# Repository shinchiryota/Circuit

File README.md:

# Circuit
2022以降の回路をまとめる

## [諸注意](諸注意)
+ [使用するソフトウェア](諸注意/使用するソフトウェア/readme.md)
+ [ファイル構成](諸注意/ファイル構成/readme.md)
+ [命名規則](諸注意/命名規則/readme.md)

## [2022](https://github.com/shinchiryota/Circuit/blob/main/2022/README.md)
+ servo_solenoidvalve_of_Tatebayashi

+ unitbase_keinz_2022

+ controller_keinz_2022
## [2023](https://github.com/shinchiryota/Circuit/blob/main/2023/README.md)
+ controller_keinz_2023

+ sensormain_of_sawada

+ servosolenoidvalve_of_tanbo

+ unitbase_anayuki
## [2024](https://github.com/shinchiryota/Circuit/blob/main/2024/README.md)
+ Power_of_Exodia

+ Unitbase_of_exoia
+ ### [nhk2024](https://github.com/shinchiryota/Circuit/blob/main/2024/nhk2024/README.md)

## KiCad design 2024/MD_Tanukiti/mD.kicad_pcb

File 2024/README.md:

# 2024年度の回路
+ Power_of_Exodia
 
+ Unitbase_of_exodia
## [nhk2024](https://github.com/shinchiryota/Circuit/tree/main/2024/nhk2024)

# [始めに戻る](https://github.com/shinchiryota/Circuit/blob/main/README.md)

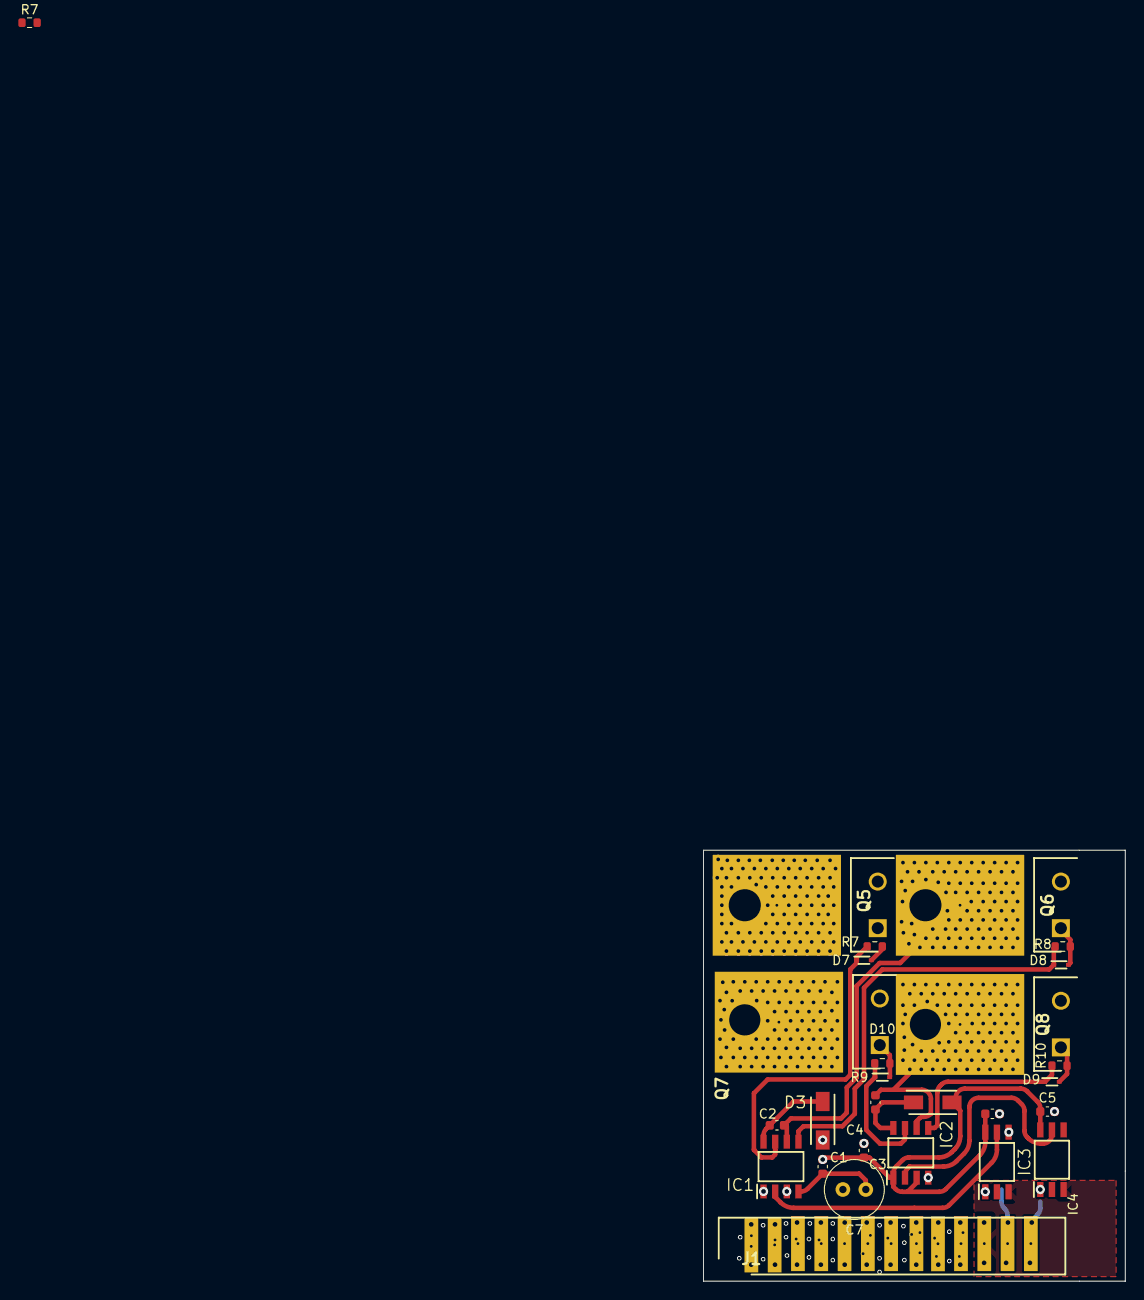
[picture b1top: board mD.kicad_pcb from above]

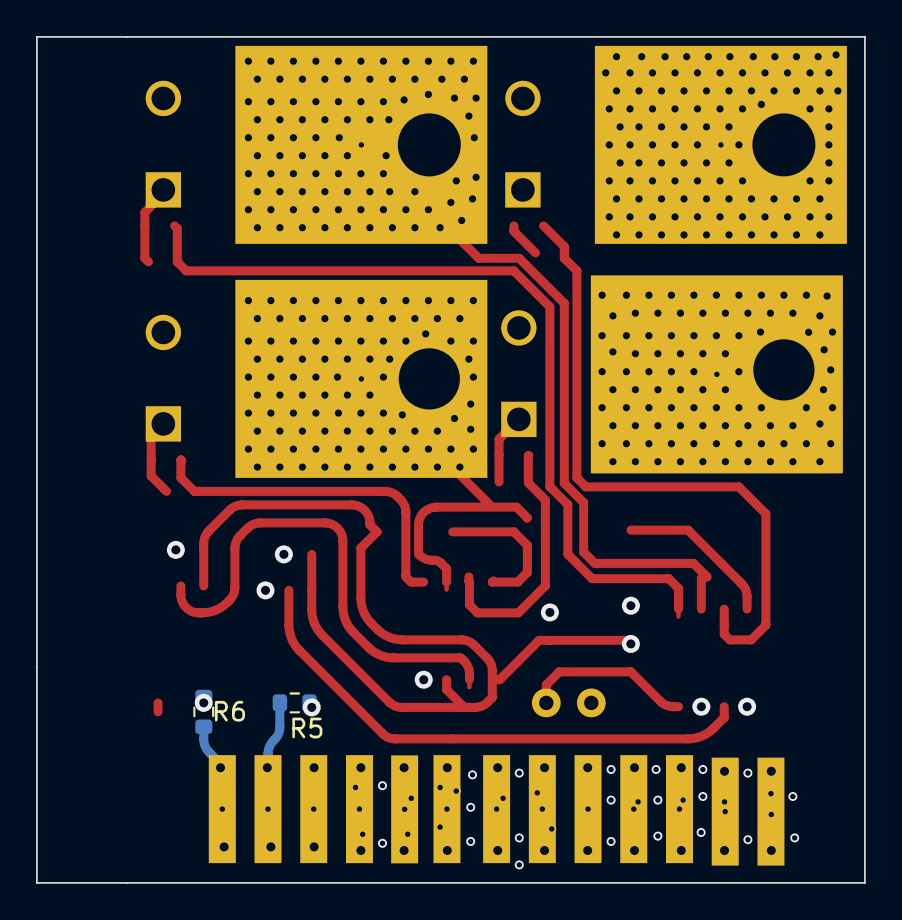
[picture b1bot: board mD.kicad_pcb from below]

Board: 2 copper layers, 46.0 x 47.0 mm, 29 parts (2 on the bottom side), 22 nets.

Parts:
C1: C_1u; C_0603_1608Metric
C2, C4: C0.1u; C_0603_1608Metric
C3: C1u; C_0603_1608Metric
C5, C6: 0.1u; C_0603_1608Metric
C7: 100uF; C_Radial_D6.3mm_H11.0mm_P2.50mm
D3, D6: SS14; DIOM5126X250N
D7, D8, D9, D10: BAT43; SODFL1608X70N
IC1, IC2: IRS2008SPBF; SOIC127P600X175-8N
IC3, IC4: TLP152_E_T; SOIC127P700X220-6N
J1: HIF3FB-26DA-2.54DSA_71_; RHDR26W71P254_2X13_3759X600X980P
Q5, Q6, Q7, Q8: EKI04027; eki04027
R5, R6: R150; R_0603_1608Metric
R7, R7#2, R8, R9, R10: 1k; R_0603_1608Metric

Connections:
/12V: C1.1, C3.1, C5.1, C6.1, C7.2, D3.2 (A), D6.2 (A), IC1.1 (VCC), IC1.3 (~SD), IC2.1 (VCC), IC2.3 (~SD), IC3.6 (VCC), IC4.6 (VCC), J1.1, J1.4, J1.6, J1.8, J1.10, Q5.2, Q7.2
/12V_GND: J1.12, J1.14, J1.16, J1.18, J1.20, Q6.3, Q8.3
/GND: IC3.3 (CATHODE), IC4.3 (CATHODE), J1.22
/GND_12V: C1.2, C3.2, C5.2, C6.2, C7.1, IC1.4 (COM), IC2.4 (COM), IC3.4 (GND), IC4.4 (GND)
/LH: D7.1 (K), IC1.7 (HO), R7.2, R7#2.2
/LIN: IC1.2 (IN), IC3.5 (VO)
/LL: D8.1 (K), IC1.5 (LO), R8.1
/LS: C2.2, IC1.6 (VS), Q5.3, Q6.2
/PWML: J1.24, R5.2
/PWMR: J1.26, R6.2
/RH: D10.1 (K), IC2.7 (HO), R9.2
/RIN: IC2.2 (IN), IC4.5 (VO)
/RL: D9.1 (K), IC2.5 (LO), R10.2
/RS: C4.2, IC2.6 (VS), Q7.3, Q8.2
unnamed: C2.1, D3.1 (K), IC1.8 (VB)
unnamed: C4.1, D6.1 (K), IC2.8 (VB)
unnamed: D7.2 (A), Q5.1, R7.1, R7#2.1
unnamed: D8.2 (A), Q6.1, R8.2
unnamed: D9.2 (A), Q8.1, R10.1
unnamed: D10.2 (A), Q7.1, R9.1
unnamed: IC3.1 (ANODE), R5.1
unnamed: IC4.1 (ANODE), R6.1

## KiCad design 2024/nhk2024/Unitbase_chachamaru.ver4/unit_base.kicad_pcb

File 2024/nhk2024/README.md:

# 高専ロボコン2024で使った回路
+ Controller 

+ Sensormain

+ Unitbase

+ Servosolenoidvalve

+ FEP02 

# [始めに戻る](https://github.com/shinchiryota/Circuit/blob/main/README.md)

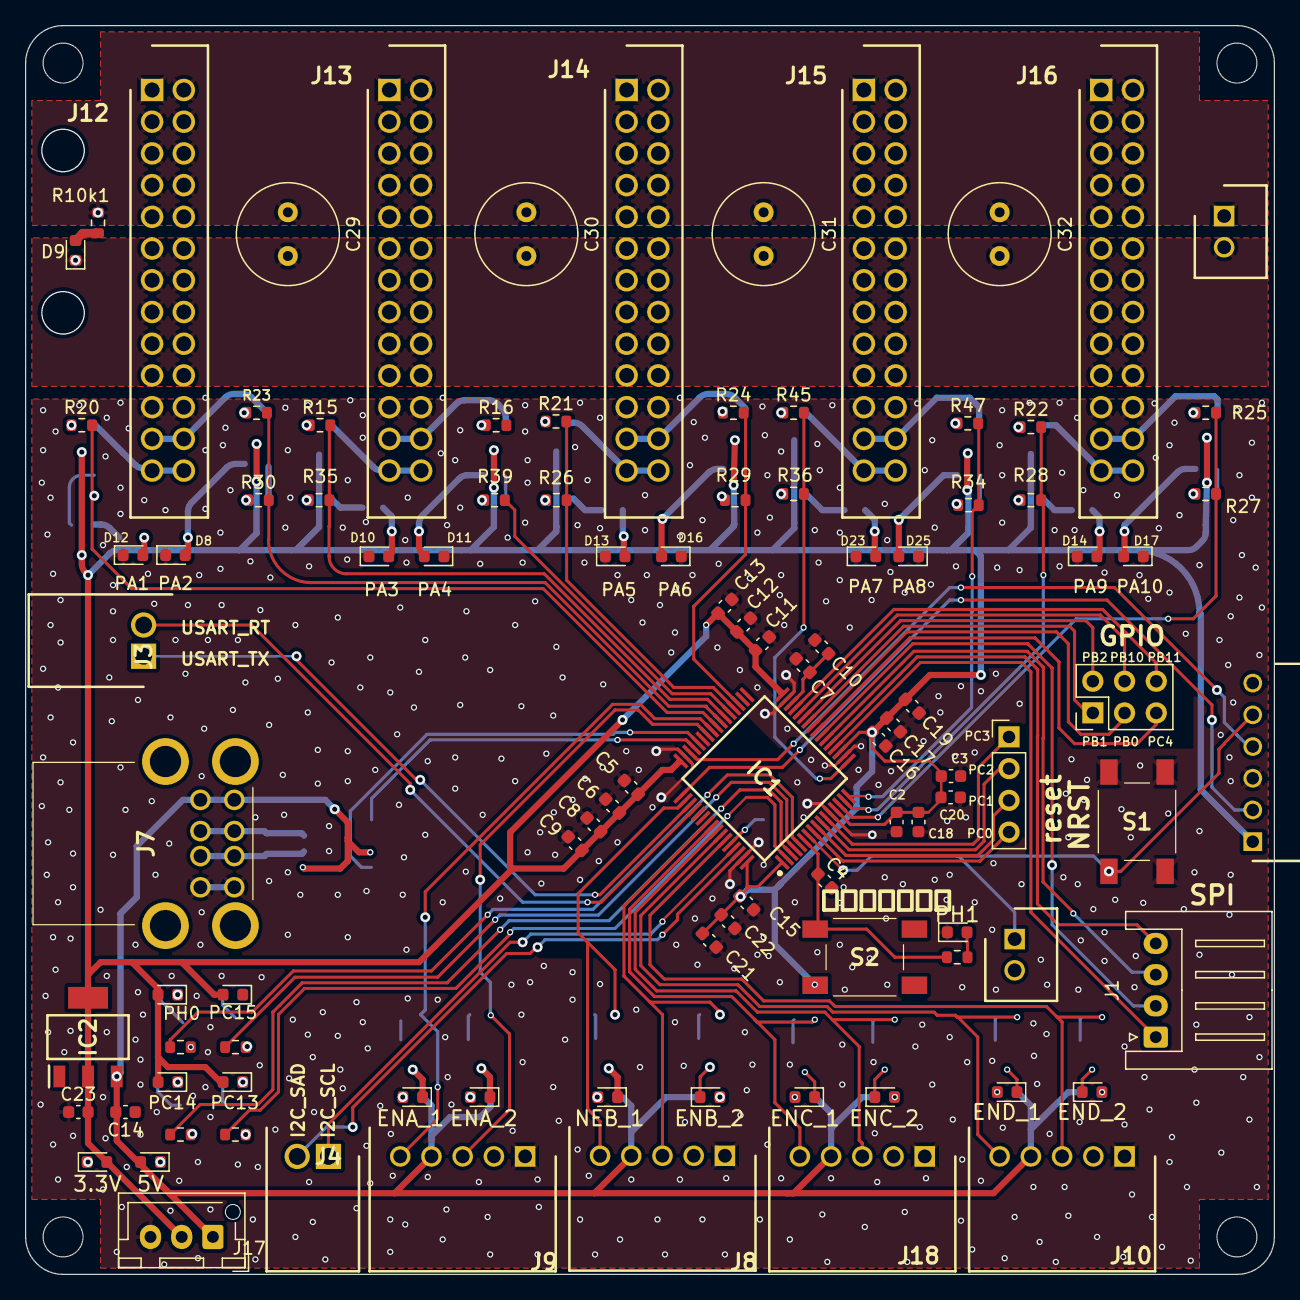
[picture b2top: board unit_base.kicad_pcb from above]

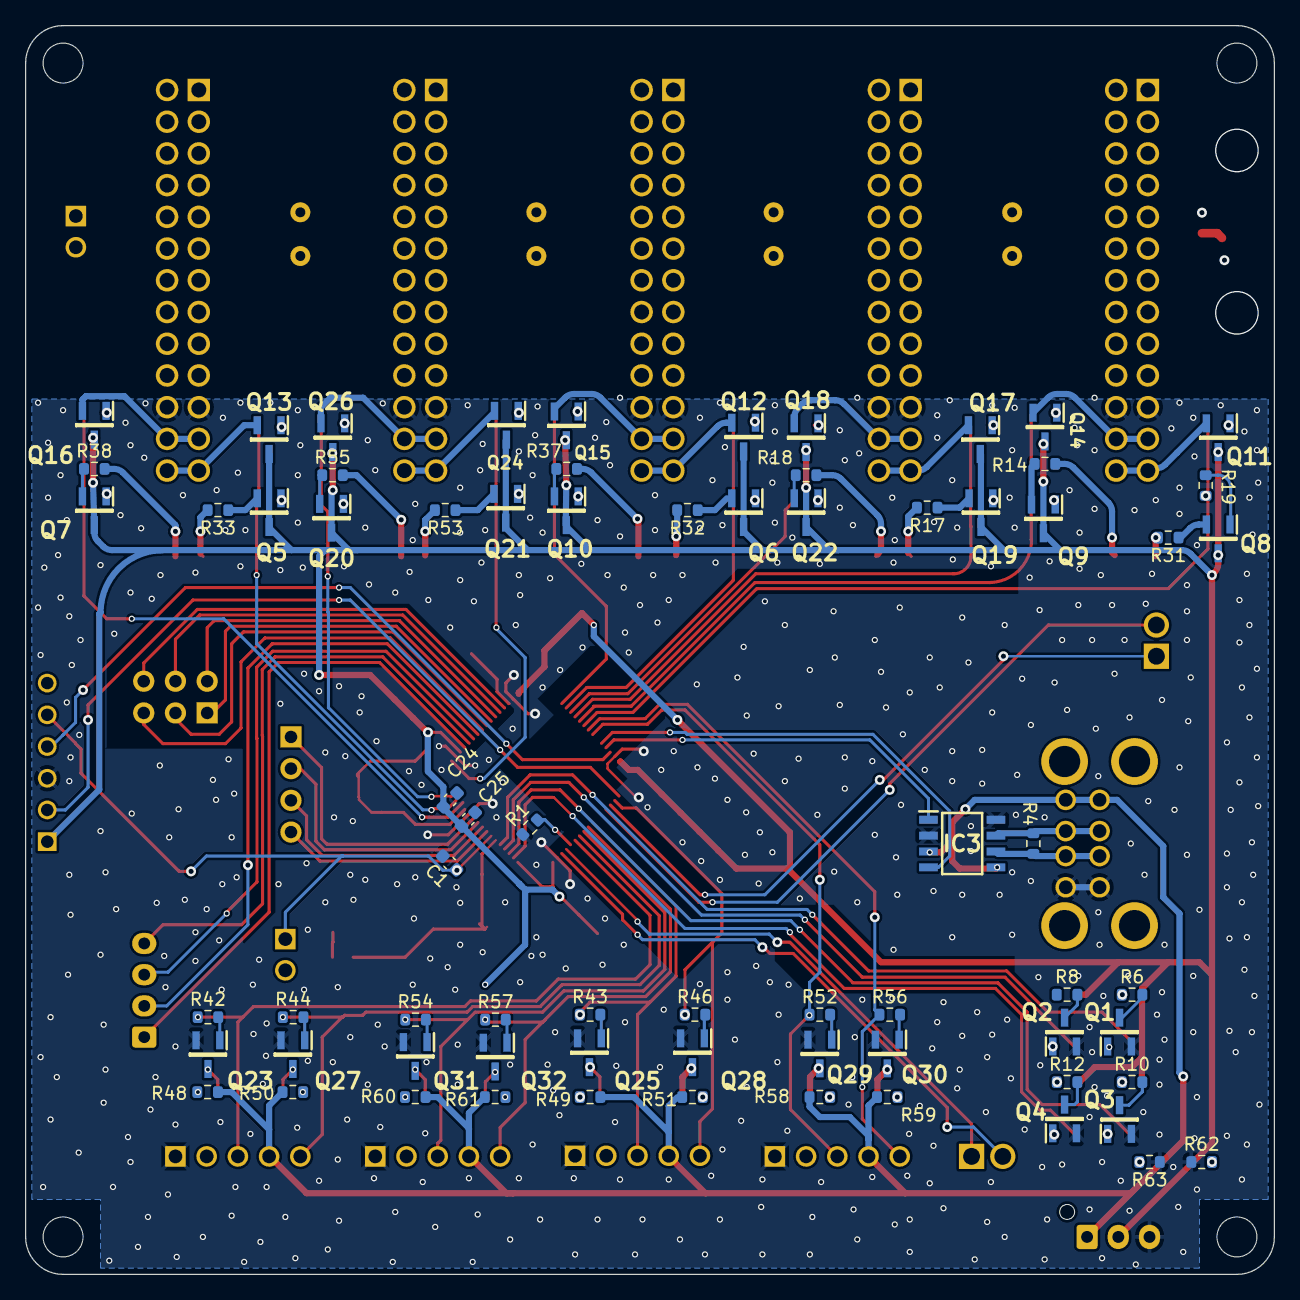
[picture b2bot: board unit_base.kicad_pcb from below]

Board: 2 copper layers, 100.0 x 100.0 mm, 169 parts (71 on the bottom side), 136 nets.

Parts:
3.3V, 5V: LED; LED_0603_1608Metric
C1, C4: C0.1u; C_0603_1608Metric
C2, C18, C24: 100n; C_0603_1608Metric
C3, C20, C25: 1u; C_0603_1608Metric
C5, C6, C8, C9, C11, C12, C13, C14, C15, C16, C17, C19: C100n; C_0603_1608Metric
C7, C10: C2.2u; C_0603_1608Metric
C21: C4.7u; C_0603_1608Metric
C22: 100u; C_0603_1608Metric
C23: C10u; C_0603_1608Metric
C29, C30, C31, C32: C; C_Radial_D8.0mm_H11.5mm_P3.50mm
D8, D9, D10, D11, D12, D13, D14, D16, D17, D23, D25: LED; LED_0603_1608Metric
ENA_1, ENA_2: LED; LED_0603_1608Metric
ENB_2: LED; LED_0603_1608Metric
ENC_1, ENC_2: LED; LED_0603_1608Metric
END_1, END_2: LED; LED_0603_1608Metric
IC1: STM32F732RET6; QFP50P1200X1200X160-64N
IC2: LM317_SOT-223_; SOT230P700X180-4N
IC3: NCV7351D1ER2G; SOIC127P600X175-8N
J1: S4B-XH-A_LF__SN_; JST_XH_S4B-XH-A_1x04_P2.50mm_Horizontal
J2, J11: B2B-XH-A; SHDR2W64P0X250_1X2_740X575X700P
J3, J4: S2B-XH-A_LF__SN_; SHDRRA2W80P0X250_1X2_740X1150X610P
J6: FH-1X06RG; RHDRRA6W58P0X254_1X6_1549X850X265P
J7: USB-4AF203AS; USB4AF203AS
J8, J9, J10, J18: S5B-XH-A_LF__SN_; SHDRRA5W64P0X250_1X5_1490X1150X610P
J12, J13, J14, J15, J16: HIF3FB-26DA-2.54DSA_71_; RHDR26W71P254_2X13_3759X600X980Pソケット
J17: B3B-XH-A; JST_XH_B3B-XH-AM_1x03_P2.50mm_Vertical
NEB_1: LED; LED_0603_1608Metric
PC13, PC14, PC15: LED; LED_0603_1608Metric
PH0, PH1: LED; LED_0603_1608Metric
Q1, Q2, Q3, Q4, Q5, Q6, Q7, Q8, Q9, Q10, Q11, Q12, Q13, Q14, Q15, Q16, Q17, Q18, Q19, Q20, Q21, Q22, Q23, Q24, Q25, Q26, Q27, Q28, Q29, Q30, Q31, Q32: 2SC2712-GR_TE85L,F; SOT95P260X156-3N
R1: R10k; R_0603_1608Metric
R2, R4, R6, R7, R8, R9, R10, R10k1, R11, R12, R13, R14, R15, R16, R17, R18, R19, R20, R21, R22, R23, R24, R25, R26, R27, R28, R29, R30, R31, R32, R33, R34, R35, R36, R37, R38, R39, R42, R43, R44, R45, R46, R47, R48, R49, R50, R51, R52, R53, R54, R55, R56, R57, R58, R59, R60, R61, R62, R63: R; R_0603_1608Metric
S1, S2: TSHA-T-2.5B2-19E; TSHAT25B219E

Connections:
3.3V: 3.3V.2 (A), C2.1, C3.1, C5.1, C6.1, C8.1, C9.1, C11.1, C12.1, C13.1, C15.1, C16.1, C17.1, C18.1, C19.1, C20.1, C21.1, C22.1, C23.2, C24.1, C25.1, IC1.1 (VBAT), IC1.13 (VREF+), IC1.19 (VDD_1), IC1.32 (VDD_2), IC1.48 (VDD_3), IC1.64 (VDD_4), IC2.2 (OUTPUT_1), IC2.4 (OUTPUT_2), J6.1, J17.2, PC13.2 (A), PC14.2 (A), PC15.2 (A), PH0.2 (A), Q5.3 (COLLECTOR), Q6.3 (COLLECTOR), Q7.3 (COLLECTOR), Q8.3 (COLLECTOR), Q9.3 (COLLECTOR), Q10.3 (COLLECTOR), Q11.3 (COLLECTOR), Q12.3 (COLLECTOR), Q13.3 (COLLECTOR), Q14.3 (COLLECTOR), Q15.3 (COLLECTOR), Q16.3 (COLLECTOR), Q17.3 (COLLECTOR), Q18.3 (COLLECTOR), Q19.3 (COLLECTOR), Q20.3 (COLLECTOR), Q21.3 (COLLECTOR), Q22.3 (COLLECTOR), Q24.3 (COLLECTOR), Q26.3 (COLLECTOR), S2.C1 (COM_1)
12V: C29.1, C30.1, C31.1, C32.1, J11.1, J12.1, J12.2, J12.3, J12.4, J12.5, J12.6, J12.7, J12.8, J12.9, J12.10, J13.1, J13.2, J13.3, J13.4, J13.5, J13.6, J13.7, J13.8, J13.9, J13.10, J14.1, J14.2, J14.3, J14.4, J14.5, J14.6, J14.7, J14.8, J14.9, J14.10, J15.1, J15.2, J15.3, J15.4, J15.5, J15.6, J15.7, J15.8, J15.9, J15.10, J16.1, J16.2, J16.3, J16.4, J16.5, J16.6, J16.7, J16.8, J16.9, J16.10, R10k1.2
12V_GND: C29.2, C30.2, C31.2, C32.2, D9.1 (K), J11.2, J12.11, J12.12, J12.13, J12.14, J12.15, J12.16, J12.17, J12.18, J12.19, J12.20, J13.11, J13.12, J13.13, J13.14, J13.15, J13.16, J13.17, J13.18, J13.19, J13.20, J14.11, J14.12, J14.13, J14.14, J14.15, J14.16, J14.17, J14.18, J14.19, J14.20, J15.11, J15.12, J15.13, J15.14, J15.15, J15.16, J15.17, J15.18, J15.19, J15.20, J16.11, J16.12, J16.13, J16.14, J16.15, J16.16, J16.17, J16.18, J16.19, J16.20
/5V: 5V.2 (A), C14.2, IC2.3 (INPUT), IC3.3 (VCC), IC3.5 (EN), J7.1, J7.5, J8.4, J9.4, J10.4, J17.1, J18.4, R48.2, R49.2, R50.2, R51.2, R58.2, R59.2, R60.2, R61.2
/5V_GND: C14.1, IC2.1 (ADJ)
/12V/PA1: J12.25, J12.26, Q11.2 (EMITTER)
/12V/PA2: J12.23, J12.24, Q14.2 (EMITTER)
/12V/PA3: J13.25, J13.26, Q17.2 (EMITTER)
/12V/PA4: J13.23, J13.24, Q18.2 (EMITTER)
/12V/PA5: J14.25, J14.26, Q12.2 (EMITTER)
/12V/PA6: J14.23, J14.24, Q15.2 (EMITTER)
/12V/PA7: J15.25, J15.26, Q24.2 (EMITTER)
/12V/PA8: J15.23, J15.24, Q26.2 (EMITTER)
/12V/PA9: J16.25, J16.26, Q13.2 (EMITTER)
/12V/PA10: J16.23, J16.24, Q16.2 (EMITTER)
/CAN1_RX: IC1.44 (PA11), IC3.4 (RXD)
/CAN1_TX: IC1.45 (PA12), IC3.1 (TXD)
/CANH: IC3.7 (CANH), J7.2, J7.6, R4.1
/CANL: IC3.6 (CANL), J7.3, J7.7, R4.2
/EncoderA_1: IC1.41 (PA8), J9.5, R56.1
/EncoderA_2: IC1.42 (PA9), J9.3, R52.1
/EncoderB_1: IC1.50 (PA15), J8.5, R46.1
/EncoderB_2: IC1.55 (PB3), J8.3, R43.1
/EncoderC_1: IC1.56 (PB4), J18.5, R57.1
/EncoderC_2: IC1.57 (PB5), J18.3, R54.1
/EncoderD_1: IC1.58 (PB6), J10.5, R44.1
/EncoderD_2: IC1.59 (PB7), J10.3, R42.1
/I2C1_SCL: IC1.61 (PB8), J4.1
/I2C1_SDA: IC1.62 (PB9), J4.2
/NRST: C1.1, IC1.7 (NRST), J2.1, J6.5, S1.A1 (NO_1)
/PH0: IC1.5 (PH0-OSC_IN), R7.2
/PH1: C4.1, IC1.6 (PH1-OSC_OUT), R2.2, S2.A1 (NO_1)
/SPI1_MISO: IC1.22 (PA6), J1.3
/SPI1_MOSI: IC1.23 (PA7), J1.2
/SPI1_NSS: IC1.20 (PA4), J1.1
/SPI1_SCK: IC1.21 (PA5), J1.4
/SWCLK: IC1.49 (PA14), J6.2
/SWDIO: IC1.46 (PA13), J6.4
/UART4_RT: IC1.52 (PC11), J3.2
/UART4_TX: IC1.51 (PC10), J3.1
/VCAP: C7.1, C10.1, IC1.30 (VCAP_1)
GND: C1.2, C2.2, C3.2, C4.2, C5.2, C6.2, C7.2, C8.2, C9.2, C10.2, C11.2, C12.2, C13.2, C15.2, C16.2, C17.2, C18.2, C19.2, C20.2, C21.2, C22.2, C23.1, D8.1 (K), D10.1 (K), D11.1 (K), D12.1 (K), D13.1 (K), D14.1 (K), D16.1 (K), D17.1 (K), D23.1 (K), D25.1 (K), IC1.12 (VSSA), IC1.18 (VSS_1), IC1.31 (VSS_2), IC1.47 (VSS_3), IC1.63 (VSS_4), IC3.2 (GND), IC3.8 (S), J6.3, J7.4, J7.8, J8.1, J9.1, J10.1, J12.21, J12.22, J13.21, J13.22, J14.21, J14.22, J15.21, J15.22, J16.21, J16.22, J17.3, J18.1, PH1.1 (K), Q1.2 (EMITTER), Q2.2 (EMITTER), Q3.2 (EMITTER), Q4.2 (EMITTER), Q23.2 (EMITTER), Q25.2 (EMITTER), Q27.2 (EMITTER), Q28.2 (EMITTER), Q29.2 (EMITTER), Q30.2 (EMITTER), Q31.2 (EMITTER), Q32.2 (EMITTER), R1.1, R62.1, R63.1, S1.B1 (NO_2), S1.C1 (COM_1), S1.D1 (COM_2)
MDA_1: IC1.40 (PC9), R19.2, R20.2
MDA_2: IC1.39 (PC8), R23.2, R30.2
MDB_1: IC1.38 (PC7), R15.2, R35.2
MDB_2: IC1.37 (PC6), R16.2, R39.2
MDC_1: IC1.36 (PB15), R21.2, R26.2
MDC_2: IC1.35 (PB14), R24.2, R29.2
MDD_1: IC1.17 (PA3), R36.2, R45.2
MDD_2: IC1.16 (PA2), R34.2, R47.2
MDE_1: IC1.15 (PA1), R22.2, R28.2
MDE_2: IC1.14 (PA0-WKUP), R25.2, R27.2
unnamed: PH1.2 (A), R2.1
unnamed: PH0.1 (K), R6.1
unnamed: PC15.1 (K), R8.1
unnamed: PC14.1 (K), R10.1
unnamed: PC13.1 (K), R12.1
unnamed: D8.2 (A), R14.2
unnamed: D9.2 (A), R10k1.1
unnamed: D10.2 (A), R17.2
unnamed: D11.2 (A), R18.2
unnamed: D12.2 (A), R31.2
unnamed: D13.2 (A), R32.2
unnamed: D14.2 (A), R33.2
unnamed: D16.2 (A), R37.2
unnamed: D17.2 (A), R38.2
unnamed: END_2.2 (A), R48.1
unnamed: END_2.1 (K), Q23.3 (COLLECTOR)
unnamed: ENB_2.2 (A), R49.1
unnamed: ENB_2.1 (K), Q25.3 (COLLECTOR)
unnamed: END_1.2 (A), R50.1
unnamed: END_1.1 (K), Q27.3 (COLLECTOR)
unnamed: NEB_1.2 (A), R51.1
unnamed: NEB_1.1 (K), Q28.3 (COLLECTOR)
unnamed: D23.2 (A), R53.2
unnamed: ENA_2.2 (A), R58.1
unnamed: ENA_2.1 (K), Q29.3 (COLLECTOR)
unnamed: D25.2 (A), R55.2
unnamed: ENA_1.2 (A), R59.1
unnamed: ENA_1.1 (K), Q30.3 (COLLECTOR)
unnamed: ENC_2.2 (A), R60.1
unnamed: ENC_2.1 (K), Q31.3 (COLLECTOR)
unnamed: ENC_1.2 (A), R61.1
unnamed: ENC_1.1 (K), Q32.3 (COLLECTOR)
unnamed: 3.3V.1 (K), R62.2
unnamed: 5V.1 (K), R63.2
unnamed: IC1.60 (BOOT0), R1.2
unnamed: Q1.1 (BASE), R7.1
unnamed: Q1.3 (COLLECTOR), R6.2
unnamed: Q2.1 (BASE), R9.1
unnamed: Q2.3 (COLLECTOR), R8.2
unnamed: Q3.1 (BASE), R11.1
unnamed: Q3.3 (COLLECTOR), R10.2
unnamed: Q4.1 (BASE), R13.1
unnamed: Q4.3 (COLLECTOR), R12.2
unnamed: Q5.1 (BASE), R28.1
unnamed: Q5.2 (EMITTER), R33.1
unnamed: Q6.1 (BASE), R26.1
unnamed: Q6.2 (EMITTER), R32.1
unnamed: Q7.1 (BASE), R27.1
unnamed: Q7.2 (EMITTER), R38.1
unnamed: Q8.1 (BASE), R19.1
unnamed: Q8.2 (EMITTER), R31.1
unnamed: Q9.1 (BASE), R30.1
unnamed: Q9.2 (EMITTER), R14.1
unnamed: Q10.1 (BASE), R29.1
unnamed: Q10.2 (EMITTER), R37.1
unnamed: Q11.1 (BASE), R20.1
unnamed: Q12.1 (BASE), R21.1
unnamed: Q13.1 (BASE), R22.1
unnamed: Q14.1 (BASE), R23.1
unnamed: Q15.1 (BASE), R24.1
unnamed: Q16.1 (BASE), R25.1
unnamed: Q17.1 (BASE), R15.1
unnamed: Q18.1 (BASE), R16.1
unnamed: Q19.1 (BASE), R35.1
unnamed: Q19.2 (EMITTER), R17.1
unnamed: Q20.1 (BASE), R34.1
unnamed: Q20.2 (EMITTER), R55.1
unnamed: Q21.1 (BASE), R36.1
unnamed: Q21.2 (EMITTER), R53.1
unnamed: Q22.1 (BASE), R39.1
unnamed: Q22.2 (EMITTER), R18.1
unnamed: Q23.1 (BASE), R42.2
unnamed: Q24.1 (BASE), R45.1
unnamed: Q25.1 (BASE), R43.2
unnamed: Q26.1 (BASE), R47.1
unnamed: Q27.1 (BASE), R44.2
unnamed: Q28.1 (BASE), R46.2
unnamed: Q29.1 (BASE), R52.2
unnamed: Q30.1 (BASE), R56.2
unnamed: Q31.1 (BASE), R54.2
unnamed: Q32.1 (BASE), R57.2
PC13: IC1.2 (PC13), R13.2
PC14: IC1.3 (PC14-OSC32_IN), R11.2
PC15: IC1.4 (PC15-OSC32_OUT), R9.2

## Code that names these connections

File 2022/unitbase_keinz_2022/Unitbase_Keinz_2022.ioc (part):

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Mcu.Name=STM32F732RETx
Mcu.Package=LQFP64
Mcu.UserName=STM32F732RETx
PA0-WKUP.GPIOParameters=GPIO_Label
PA0-WKUP.GPIO_Label=MD5_a
PA0-WKUP.Signal=S_TIM5_CH1
PA1.GPIOParameters=GPIO_Label
PA1.GPIO_Label=MD5_b
PA1.Signal=S_TIM5_CH2
PA11.Mode=CAN_Activate
PA11.Signal=CAN1_RX
PA12.Mode=CAN_Activate
PA12.Signal=CAN1_TX
PA13.Mode=Serial_Wire
PA13.Signal=SYS_JTMS-SWDIO
PA14.Mode=Serial_Wire
PA14.Signal=SYS_JTCK-SWCLK
PA15.Mode=NSS_Signal_Hard_Input
PA15.Signal=SPI3_NSS
PA2.GPIOParameters=GPIO_Label
PA2.GPIO_Label=MD2_a
PA2.Signal=S_TIM2_CH3
PA3.GPIOParameters=GPIO_Label
PA3.GPIO_Label=MD2_b
PA3.Signal=S_TIM2_CH4
PA5.GPIOParameters=GPIO_Label
PA5.GPIO_Label=MD1_a
PA5.Signal=S_TIM2_CH1_ETR
PA6.GPIOParameters=GPIO_Label
PA6.GPIO_Label=MD3_a
PA6.Signal=S_TIM3_CH1
PA7.GPIOParameters=GPIO_Label
PA7.GPIO_Label=MD3_b
PA7.Signal=S_TIM3_CH2
PA8.GPIOParameters=GPIO_Label
PA8.GPIO_Label=En1a
PA8.Signal=S_TIM1_CH1
PA9.GPIOParameters=GPIO_Label
PA9.GPIO_Label=En1b
PA9.Signal=S_TIM1_CH2
PB0.GPIOParameters=GPIO_Label
PB0.GPIO_Label=MD4_a
PB0.Signal=S_TIM3_CH3
PB1.GPIOParameters=GPIO_Label
PB1.GPIO_Label=MD4_b
PB1.Signal=S_TIM3_CH4
PB10.Mode=I2C
PB10.Signal=I2C2_SCL
PB11.Mode=I2C
PB11.Signal=I2C2_SDA
PB12.Signal=GPIO_Output
PB13.Signal=GPIO_Output
PB14.Signal=GPIO_Output
PB3.GPIOParameters=GPIO_Label
PB3.GPIO_Label=MD1_b
PB3.Signal=S_TIM2_CH2
PB6.Mode=Asynchronous
PB6.Signal=USART1_TX
PB7.Mode=Asynchronous
PB7.Signal=USART1_RX
PC1.Signal=GPIO_Output
PC10.Mode=Full_Duplex_Master
PC10.Signal=SPI3_SCK
PC11.Mode=Full_Duplex_Master
PC11.Signal=SPI3_MISO
PC12.Mode=Full_Duplex_Master
PC12.Signal=SPI3_MOSI
PC14-OSC32_IN.Signal=GPIO_Output
PC15-OSC32_OUT.Signal=GPIO_Input
PC2.Signal=GPIO_Output
PC3.Signal=GPIO_Output
PC6.GPIOParameters=GPIO_Label
PC6.GPIO_Label=En2a
PC6.Signal=S_TIM8_CH1
PC7.GPIOParameters=GPIO_Label
PC7.GPIO_Label=En2b
PC7.Signal=S_TIM8_CH2
PH0-OSC_IN.Signal=GPIO_Output
PH1-OSC_OUT.Signal=GPIO_Output
RCC.HSE_VALUE=25000000
board=custom

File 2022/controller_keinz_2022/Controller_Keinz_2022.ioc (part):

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Mcu.Name=STM32F302C(6-8)Tx
Mcu.Package=LQFP48
Mcu.UserName=STM32F302C8Tx
PA0.Signal=GPIO_Output
PA1.Signal=GPIO_Output
PA10.Mode=Asynchronous
PA10.Signal=USART1_RX
PA11.Mode=CTS_RTS
PA11.Signal=USART1_CTS
PA12.Mode=CTS_RTS
PA12.Signal=USART1_RTS
PA13.Mode=Serial_Wire
PA13.Signal=SYS_JTMS-SWDIO
PA14.Mode=Serial_Wire
PA14.Signal=SYS_JTCK-SWCLK
PA15.Mode=NSS_Signal_Hard_Input
PA15.Signal=SPI3_NSS
PA2.Signal=GPIO_Output
PA3.Signal=GPIO_Output
PA5.Signal=GPIO_Output
PA6.Signal=GPIO_Output
PA7.Signal=GPIO_Output
PA9.Mode=Asynchronous
PA9.Signal=USART1_TX
PB0.Signal=GPIO_Output
PB1.Signal=GPIO_Output
PB10.Signal=GPIO_Output
PB11.Signal=GPIO_Output
PB12.Signal=GPIO_Output
PB13.Signal=GPIO_Output
PB14.Signal=GPIO_Output
PB15.Signal=GPIO_Output
PB2.Signal=GPIO_Output
PB3.Mode=Full_Duplex_Master
PB3.Signal=SPI3_SCK
PB4.Mode=Full_Duplex_Master
PB4.Signal=SPI3_MISO
PB5.Mode=Full_Duplex_Master
PB5.Signal=SPI3_MOSI
PB6.Mode=I2C
PB6.Signal=I2C1_SCL
PB7.Mode=I2C
PB7.Signal=I2C1_SDA
PC13.Signal=GPIO_Output
PF0-OSC_IN.Mode=I2C
PF0-OSC_IN.Signal=I2C2_SDA
PF1-OSC_OUT.Mode=I2C
PF1-OSC_OUT.Signal=I2C2_SCL
RCC.HSEPLLFreq_Value=8000000
RCC.HSE_VALUE=8000000
RCC.SYSCLKFreq_VALUE=8000000
board=custom

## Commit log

2024-04-13 高専ロボコン2024のときに作成された回路を示すフォルダーを作成した
2024-04-13 zipファイルを解凍,ファイルの整備性を良くした
